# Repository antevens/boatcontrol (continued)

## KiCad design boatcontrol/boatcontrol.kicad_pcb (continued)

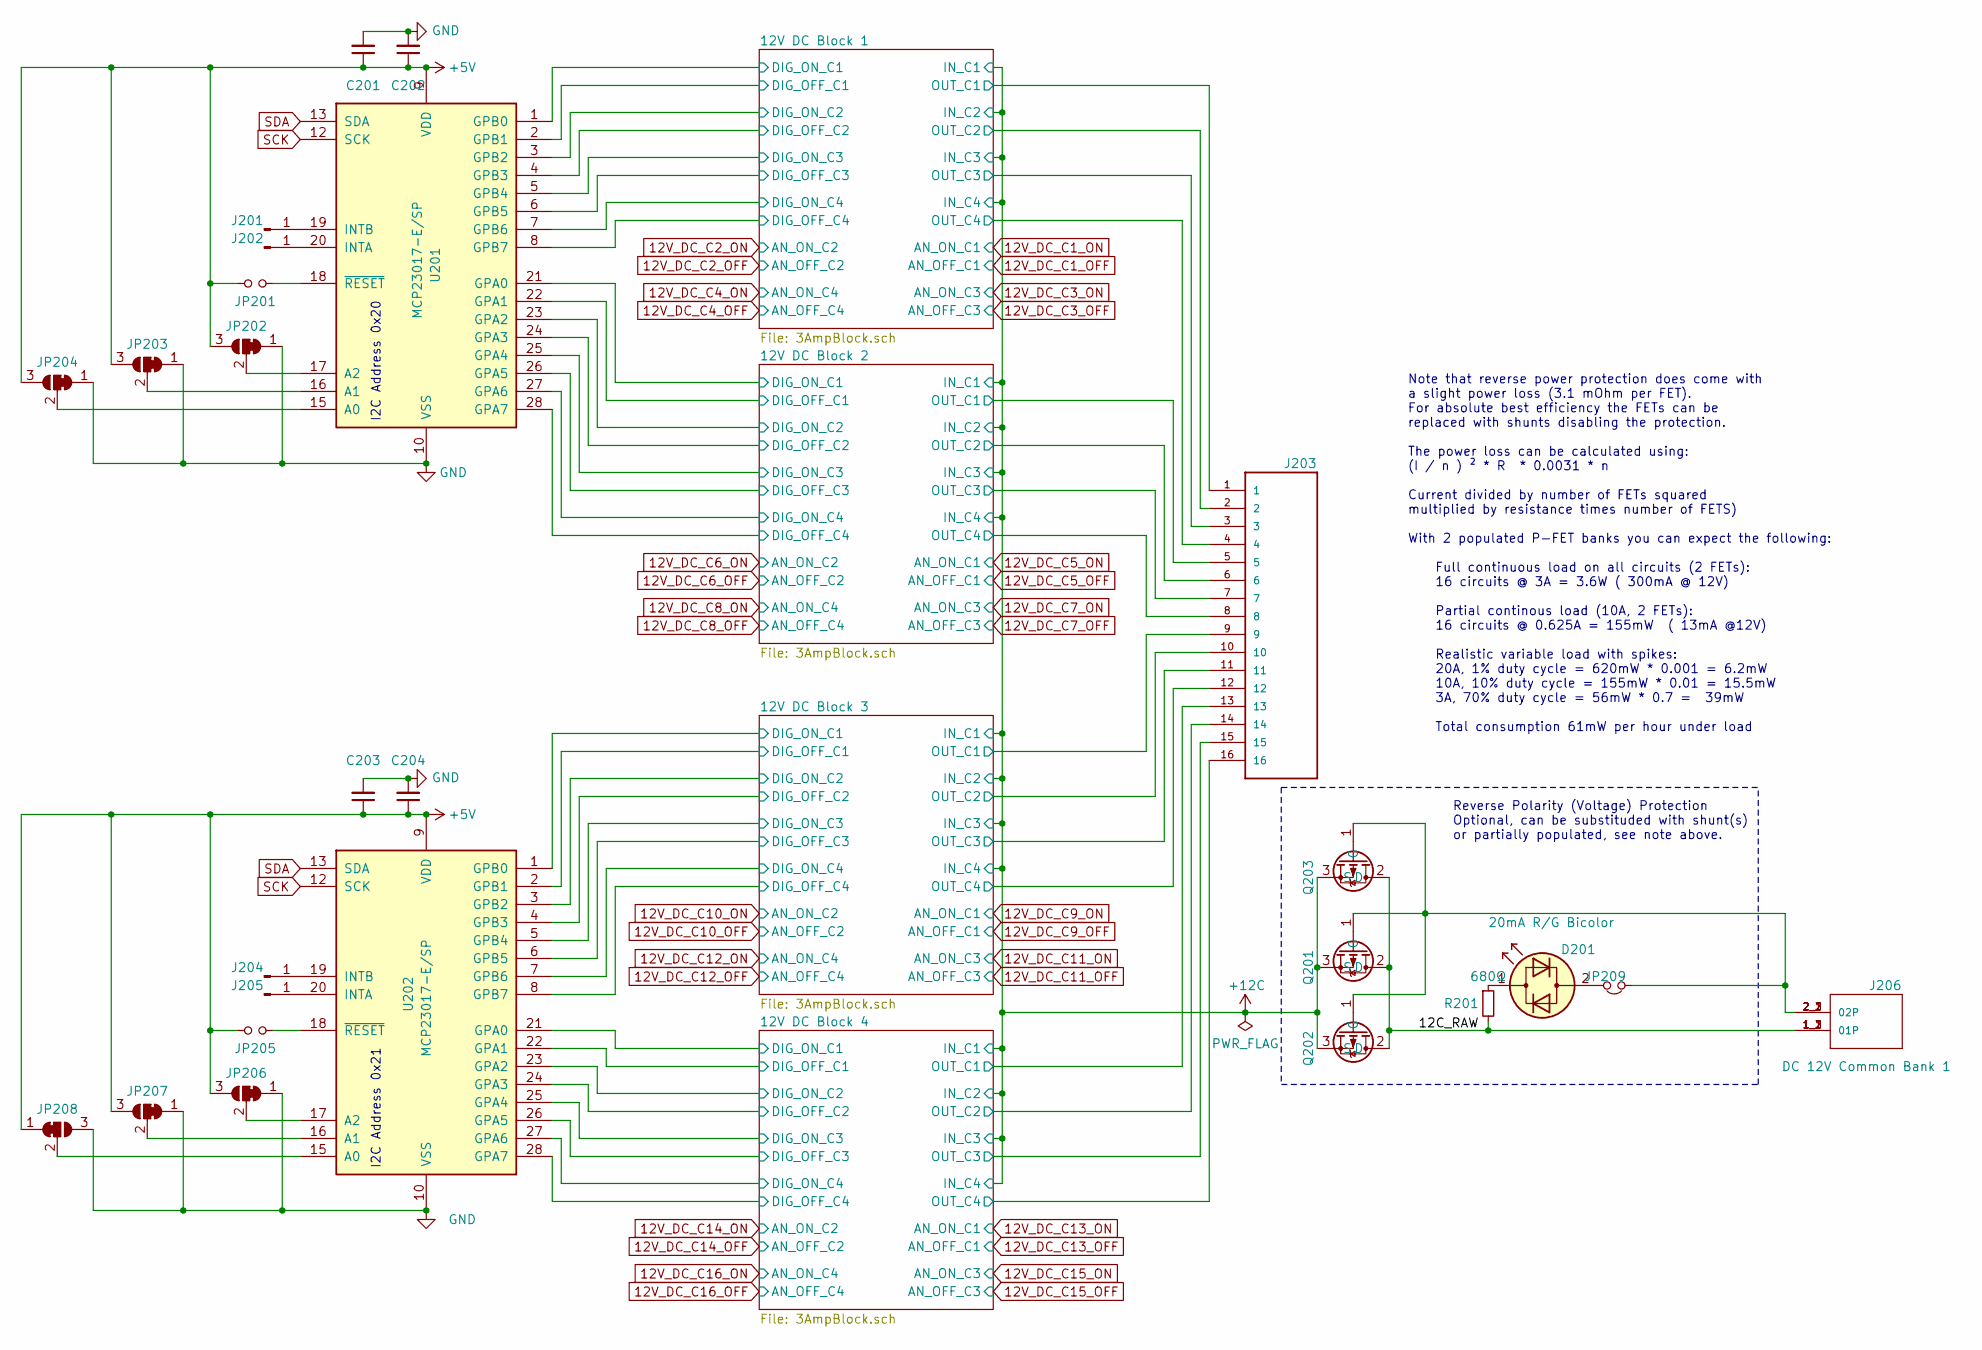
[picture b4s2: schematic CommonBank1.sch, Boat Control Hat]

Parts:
C201, C203: 10μF; C_Disc_D7.5mm_W5.0mm_P5.00mm
C202, C204: 0.1μF; C_Disc_D7.5mm_W5.0mm_P5.00mm
D201: 20mA R/G Bicolor; LED_D5.0mm
J201, J202, J204, J205: Conn_01x01_Male; PinHeader_1x01_P2.54mm_Vertical
J203: TBP01R2W-508-16BE; CUI_TBP01R2W-508-16BE
J206: TBL008V-1000-02BE; CUI_TBL008V-1000-02BE
JP201, JP205: Jumper_NO_Small; PinHeader_1x02_P2.54mm_Vertical
JP202, JP203, JP204, JP206, JP207, JP208: SolderJumper_3_Bridged12; SolderJumper-3_P1.3mm_Bridged12_RoundedPad1.0x1.5mm
JP209: Jumper_NC_Small; PinHeader_1x02_P2.54mm_Vertical
Q201, Q202, Q203: IPP120P04P4L-03; TO-220-3_Vertical
R201: 680Ω; R_Axial_DIN0207_L6.3mm_D2.5mm_P7.62mm_Horizontal
U201, U202: MCP23017-E/SP; DIP-28_W7.62mm

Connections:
+5V: C201.1, C202.1, C203.1, C204.1, JP201.2, JP202.3 (B), JP203.3 (B), JP204.3 (B), JP205.2, JP206.3 (B), JP207.3 (B), JP208.1 (A), U201.9 (VDD), U202.9 (VDD); also elsewhere on the board
+12C: Q201.3 (S), Q202.3 (S), Q203.3 (S); also elsewhere on the board
/12V DC Common Bank/12C_RAW: J206.1_1 (01P), J206.1_2 (01P), J206.1_3 (01P), Q201.2 (D), Q202.2 (D), Q203.2 (D), R201.2
/12V DC Common Bank/12V DC Block 1/DIG_OFF_C1: U201.2 (GPB1); also elsewhere on the board
/12V DC Common Bank/12V DC Block 1/DIG_OFF_C2: U201.4 (GPB3); also elsewhere on the board
/12V DC Common Bank/12V DC Block 1/DIG_OFF_C3: U201.6 (GPB5); also elsewhere on the board
/12V DC Common Bank/12V DC Block 1/DIG_OFF_C4: U201.8 (GPB7); also elsewhere on the board
/12V DC Common Bank/12V DC Block 1/DIG_ON_C1: U201.1 (GPB0); also elsewhere on the board
/12V DC Common Bank/12V DC Block 1/DIG_ON_C2: U201.3 (GPB2); also elsewhere on the board
/12V DC Common Bank/12V DC Block 1/DIG_ON_C3: U201.5 (GPB4); also elsewhere on the board
/12V DC Common Bank/12V DC Block 1/DIG_ON_C4: U201.7 (GPB6); also elsewhere on the board
/12V DC Common Bank/12V DC Block 1/OUT_C1: J203.1; also elsewhere on the board
/12V DC Common Bank/12V DC Block 1/OUT_C2: J203.2; also elsewhere on the board
/12V DC Common Bank/12V DC Block 1/OUT_C3: J203.3; also elsewhere on the board
/12V DC Common Bank/12V DC Block 1/OUT_C4: J203.4; also elsewhere on the board
/12V DC Common Bank/12V DC Block 2/DIG_OFF_C1: U201.22 (GPA1); also elsewhere on the board
/12V DC Common Bank/12V DC Block 2/DIG_OFF_C2: U201.24 (GPA3); also elsewhere on the board
/12V DC Common Bank/12V DC Block 2/DIG_OFF_C3: U201.26 (GPA5); also elsewhere on the board
/12V DC Common Bank/12V DC Block 2/DIG_OFF_C4: U201.28 (GPA7); also elsewhere on the board
/12V DC Common Bank/12V DC Block 2/DIG_ON_C1: U201.21 (GPA0); also elsewhere on the board
/12V DC Common Bank/12V DC Block 2/DIG_ON_C2: U201.23 (GPA2); also elsewhere on the board
/12V DC Common Bank/12V DC Block 2/DIG_ON_C3: U201.25 (GPA4); also elsewhere on the board
/12V DC Common Bank/12V DC Block 2/DIG_ON_C4: U201.27 (GPA6); also elsewhere on the board
/12V DC Common Bank/12V DC Block 2/OUT_C1: J203.5; also elsewhere on the board
/12V DC Common Bank/12V DC Block 2/OUT_C2: J203.6; also elsewhere on the board
/12V DC Common Bank/12V DC Block 2/OUT_C3: J203.7; also elsewhere on the board
/12V DC Common Bank/12V DC Block 2/OUT_C4: J203.8; also elsewhere on the board
/12V DC Common Bank/12V DC Block 3/DIG_OFF_C1: U202.2 (GPB1); also elsewhere on the board
/12V DC Common Bank/12V DC Block 3/DIG_OFF_C2: U202.4 (GPB3); also elsewhere on the board
/12V DC Common Bank/12V DC Block 3/DIG_OFF_C3: U202.6 (GPB5); also elsewhere on the board
/12V DC Common Bank/12V DC Block 3/DIG_OFF_C4: U202.8 (GPB7); also elsewhere on the board
/12V DC Common Bank/12V DC Block 3/DIG_ON_C1: U202.1 (GPB0); also elsewhere on the board
/12V DC Common Bank/12V DC Block 3/DIG_ON_C2: U202.3 (GPB2); also elsewhere on the board
/12V DC Common Bank/12V DC Block 3/DIG_ON_C3: U202.5 (GPB4); also elsewhere on the board
/12V DC Common Bank/12V DC Block 3/DIG_ON_C4: U202.7 (GPB6); also elsewhere on the board
/12V DC Common Bank/12V DC Block 3/OUT_C1: J203.9; also elsewhere on the board
/12V DC Common Bank/12V DC Block 3/OUT_C2: J203.10; also elsewhere on the board
/12V DC Common Bank/12V DC Block 3/OUT_C3: J203.11; also elsewhere on the board
/12V DC Common Bank/12V DC Block 3/OUT_C4: J203.12; also elsewhere on the board
/12V DC Common Bank/12V DC Block 4/DIG_OFF_C1: U202.22 (GPA1); also elsewhere on the board
/12V DC Common Bank/12V DC Block 4/DIG_OFF_C2: U202.24 (GPA3); also elsewhere on the board
/12V DC Common Bank/12V DC Block 4/DIG_OFF_C3: U202.26 (GPA5); also elsewhere on the board
/12V DC Common Bank/12V DC Block 4/DIG_OFF_C4: U202.28 (GPA7); also elsewhere on the board
/12V DC Common Bank/12V DC Block 4/DIG_ON_C1: U202.21 (GPA0); also elsewhere on the board
/12V DC Common Bank/12V DC Block 4/DIG_ON_C2: U202.23 (GPA2); also elsewhere on the board
/12V DC Common Bank/12V DC Block 4/DIG_ON_C3: U202.25 (GPA4); also elsewhere on the board
/12V DC Common Bank/12V DC Block 4/DIG_ON_C4: U202.27 (GPA6); also elsewhere on the board
/12V DC Common Bank/12V DC Block 4/OUT_C1: J203.13; also elsewhere on the board
/12V DC Common Bank/12V DC Block 4/OUT_C2: J203.14; also elsewhere on the board
/12V DC Common Bank/12V DC Block 4/OUT_C3: J203.15; also elsewhere on the board
/12V DC Common Bank/12V DC Block 4/OUT_C4: J203.16; also elsewhere on the board
GND: C201.2, C202.2, C203.2, C204.2, JP202.1 (A), JP203.1 (A), JP204.1 (A), JP206.1 (A), JP207.1 (A), JP208.3 (B), U201.10 (VSS), U202.10 (VSS); also elsewhere on the board
unnamed: D201.1 (KA), R201.1
unnamed: D201.2 (AK), JP209.2
unnamed: J201.1, U201.19 (INTB)
unnamed: J202.1, U201.20 (INTA)
unnamed: J204.1, U202.19 (INTB)
unnamed: J205.1, U202.20 (INTA)
unnamed: J206.2_1 (02P), J206.2_2 (02P), J206.2_3 (02P), JP209.1, Q201.1 (G), Q202.1 (G), Q203.1 (G)
unnamed: JP201.1, U201.18 (~RESET~)
unnamed: JP202.2 (C), U201.17 (A2)
unnamed: JP203.2 (C), U201.16 (A1)
unnamed: JP204.2 (C), U201.15 (A0)
unnamed: JP205.1, U202.18 (~RESET~)
unnamed: JP206.2 (C), U202.17 (A2)
unnamed: JP207.2 (C), U202.16 (A1)
unnamed: JP208.2 (C), U202.15 (A0)
SCK: U201.12 (SCK), U202.12 (SCK); also elsewhere on the board
SDA: U201.13 (SDA), U202.13 (SDA); also elsewhere on the board

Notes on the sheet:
I2C Address 0x20
I2C Address 0x21
Reverse Polarity (Voltage) Protection Optional, can be substituded with shunt(s) or partially populated, see note above.
Note that reverse power protection does come with a slight power loss (3.1 mOhm per FET). For absolute best efficiency the FETs can be replaced with shunts disabling the protection. The power loss can be calculated using: (I / n ) ² * R * 0.0031 * n Current divided by number of FETs squared multipl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

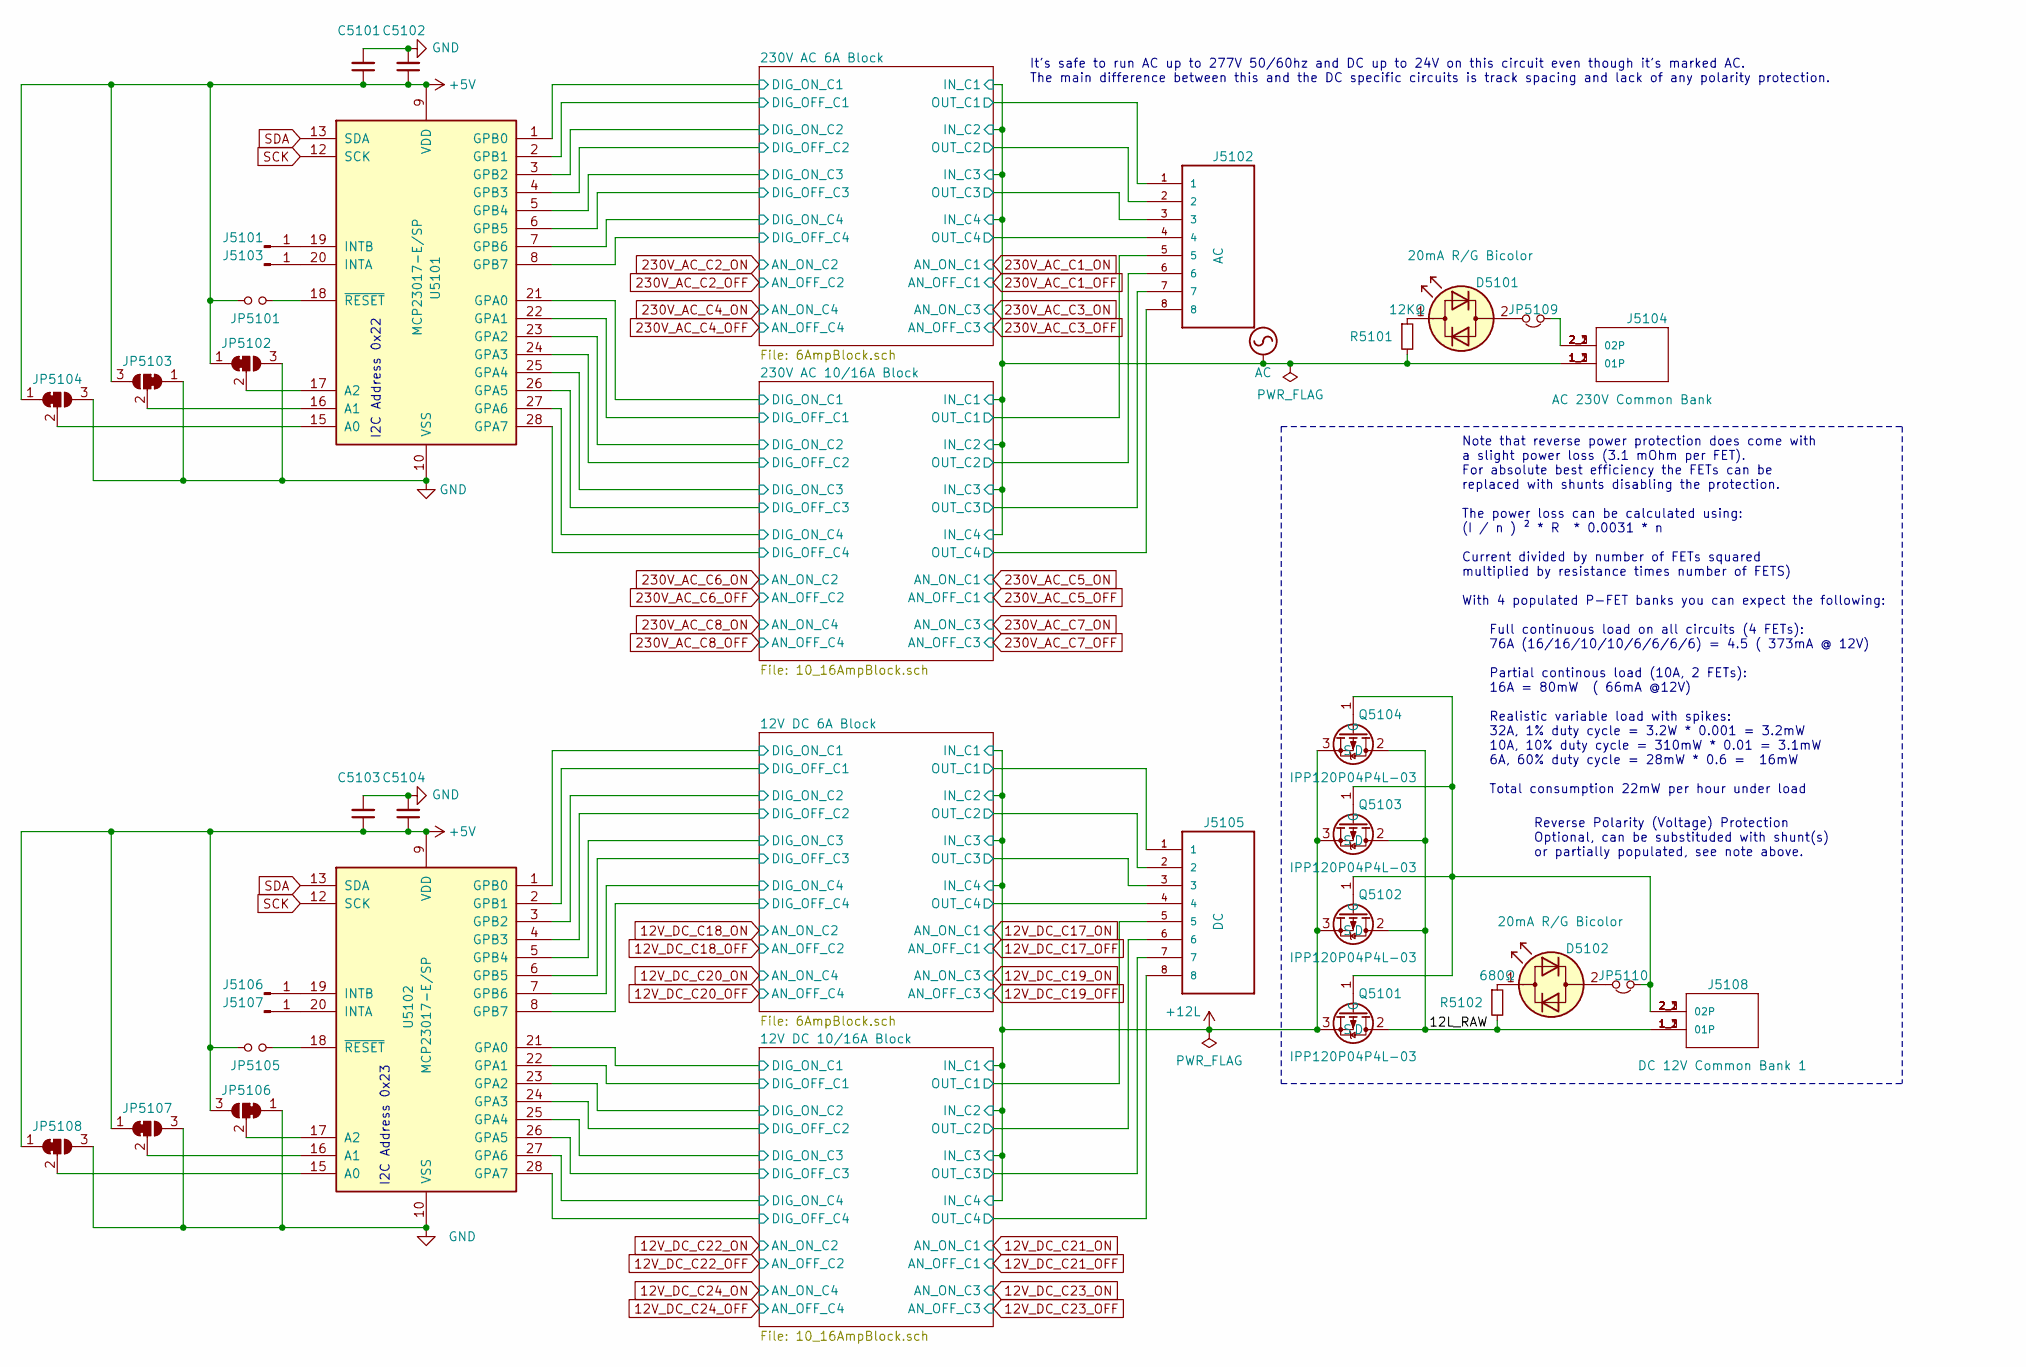
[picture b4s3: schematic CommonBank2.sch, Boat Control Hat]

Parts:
C5101, C5103: 10μF; C_Disc_D7.5mm_W5.0mm_P5.00mm
C5102, C5104: 0.1μF; C_Disc_D7.5mm_W5.0mm_P5.00mm
D5101, D5102: 20mA R/G Bicolor; LED_D5.0mm
J5101, J5103, J5106, J5107: Conn_01x01_Male; PinHeader_1x01_P2.54mm_Vertical
J5102, J5105: TBP01R2W-508-08BE; CUI_TBP01R2W-508-08BE
J5104, J5108: TBL008V-1000-02BE; CUI_TBL008V-1000-02BE
JP5101, JP5105: Jumper_NO_Small; PinHeader_1x02_P2.54mm_Vertical
JP5102, JP5103, JP5104, JP5106, JP5107, JP5108: SolderJumper_3_Bridged12; SolderJumper-3_P1.3mm_Bridged12_RoundedPad1.0x1.5mm
JP5109, JP5110: Jumper_NC_Small; PinHeader_1x02_P2.54mm_Vertical
Q5101, Q5102, Q5103, Q5104: IPP120P04P4L-03; TO-220-3_Vertical
R5101: 12KΩ; R_Axial_DIN0207_L6.3mm_D2.5mm_P7.62mm_Horizontal
R5102: 680Ω; R_Axial_DIN0207_L6.3mm_D2.5mm_P7.62mm_Horizontal
U5101, U5102: MCP23017-E/SP; DIP-28_W7.62mm

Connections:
+5V: C5101.1, C5102.1, C5103.1, C5104.1, JP5101.2, JP5102.1 (A), JP5103.3 (B), JP5104.1 (A), JP5105.2, JP5106.3 (B), JP5107.1 (A), JP5108.1 (A), U5101.9 (VDD), U5102.9 (VDD); also elsewhere on the board
+12L: Q5101.3 (S), Q5102.3 (S), Q5103.3 (S), Q5104.3 (S); also elsewhere on the board
/Mixed 12V DC / 230V AC Common Bank/12L_RAW: J5108.1_1 (01P), J5108.1_2 (01P), J5108.1_3 (01P), Q5101.2 (D), Q5102.2 (D), Q5103.2 (D), Q5104.2 (D), R5102.2
/Mixed 12V DC / 230V AC Common Bank/12V DC 6A Block/DIG_OFF_C1: U5102.2 (GPB1); also elsewhere on the board
/Mixed 12V DC / 230V AC Common Bank/12V DC 6A Block/DIG_OFF_C2: U5102.4 (GPB3); also elsewhere on the board
/Mixed 12V DC / 230V AC Common Bank/12V DC 6A Block/DIG_OFF_C3: U5102.6 (GPB5); also elsewhere on the board
/Mixed 12V DC / 230V AC Common Bank/12V DC 6A Block/DIG_OFF_C4: U5102.8 (GPB7); also elsewhere on the board
/Mixed 12V DC / 230V AC Common Bank/12V DC 6A Block/DIG_ON_C1: U5102.1 (GPB0); also elsewhere on the board
/Mixed 12V DC / 230V AC Common Bank/12V DC 6A Block/DIG_ON_C2: U5102.3 (GPB2); also elsewhere on the board
/Mixed 12V DC / 230V AC Common Bank/12V DC 6A Block/DIG_ON_C3: U5102.5 (GPB4); also elsewhere on the board
/Mixed 12V DC / 230V AC Common Bank/12V DC 6A Block/DIG_ON_C4: U5102.7 (GPB6); also elsewhere on the board
/Mixed 12V DC / 230V AC Common Bank/12V DC 6A Block/OUT_C1: J5105.1; also elsewhere on the board
/Mixed 12V DC / 230V AC Common Bank/12V DC 6A Block/OUT_C2: J5105.2; also elsewhere on the board
/Mixed 12V DC / 230V AC Common Bank/12V DC 6A Block/OUT_C3: J5105.3; also elsewhere on the board
/Mixed 12V DC / 230V AC Common Bank/12V DC 6A Block/OUT_C4: J5105.4; also elsewhere on the board
/Mixed 12V DC / 230V AC Common Bank/12V DC 10/16A Block/DIG_OFF_C1: U5102.22 (GPA1); also elsewhere on the board
/Mixed 12V DC / 230V AC Common Bank/12V DC 10/16A Block/DIG_OFF_C2: U5102.24 (GPA3); also elsewhere on the board
/Mixed 12V DC / 230V AC Common Bank/12V DC 10/16A Block/DIG_OFF_C3: U5102.26 (GPA5); also elsewhere on the board
/Mixed 12V DC / 230V AC Common Bank/12V DC 10/16A Block/DIG_OFF_C4: U5102.28 (GPA7); also elsewhere on the board
/Mixed 12V DC / 230V AC Common Bank/12V DC 10/16A Block/DIG_ON_C1: U5102.21 (GPA0); also elsewhere on the board
/Mixed 12V DC / 230V AC Common Bank/12V DC 10/16A Block/DIG_ON_C2: U5102.23 (GPA2); also elsewhere on the board
/Mixed 12V DC / 230V AC Common Bank/12V DC 10/16A Block/DIG_ON_C3: U5102.25 (GPA4); also elsewhere on the board
/Mixed 12V DC / 230V AC Common Bank/12V DC 10/16A Block/DIG_ON_C4: U5102.27 (GPA6); also elsewhere on the board
/Mixed 12V DC / 230V AC Common Bank/12V DC 10/16A Block/OUT_C1: J5105.5; also elsewhere on the board
/Mixed 12V DC / 230V AC Common Bank/12V DC 10/16A Block/OUT_C2: J5105.6; also elsewhere on the board
/Mixed 12V DC / 230V AC Common Bank/12V DC 10/16A Block/OUT_C3: J5105.7; also elsewhere on the board
/Mixed 12V DC / 230V AC Common Bank/12V DC 10/16A Block/OUT_C4: J5105.8; also elsewhere on the board
/Mixed 12V DC / 230V AC Common Bank/230V AC 6A Block/DIG_OFF_C1: U5101.2 (GPB1); also elsewhere on the board
/Mixed 12V DC / 230V AC Common Bank/230V AC 6A Block/DIG_OFF_C2: U5101.4 (GPB3); also elsewhere on the board
/Mixed 12V DC / 230V AC Common Bank/230V AC 6A Block/DIG_OFF_C3: U5101.6 (GPB5); also elsewhere on the board
/Mixed 12V DC / 230V AC Common Bank/230V AC 6A Block/DIG_OFF_C4: U5101.8 (GPB7); also elsewhere on the board
/Mixed 12V DC / 230V AC Common Bank/230V AC 6A Block/DIG_ON_C1: U5101.1 (GPB0); also elsewhere on the board
/Mixed 12V DC / 230V AC Common Bank/230V AC 6A Block/DIG_ON_C2: U5101.3 (GPB2); also elsewhere on the board
/Mixed 12V DC / 230V AC Common Bank/230V AC 6A Block/DIG_ON_C3: U5101.5 (GPB4); also elsewhere on the board
/Mixed 12V DC / 230V AC Common Bank/230V AC 6A Block/DIG_ON_C4: U5101.7 (GPB6); also elsewhere on the board
/Mixed 12V DC / 230V AC Common Bank/230V AC 6A Block/OUT_C1: J5102.1; also elsewhere on the board
/Mixed 12V DC / 230V AC Common Bank/230V AC 6A Block/OUT_C2: J5102.2; also elsewhere on the board
/Mixed 12V DC / 230V AC Common Bank/230V AC 6A Block/OUT_C3: J5102.3; also elsewhere on the board
/Mixed 12V DC / 230V AC Common Bank/230V AC 6A Block/OUT_C4: J5102.4; also elsewhere on the board
/Mixed 12V DC / 230V AC Common Bank/230V AC 10/16A Block/DIG_OFF_C1: U5101.22 (GPA1); also elsewhere on the board
/Mixed 12V DC / 230V AC Common Bank/230V AC 10/16A Block/DIG_OFF_C2: U5101.24 (GPA3); also elsewhere on the board
/Mixed 12V DC / 230V AC Common Bank/230V AC 10/16A Block/DIG_OFF_C3: U5101.26 (GPA5); also elsewhere on the board
/Mixed 12V DC / 230V AC Common Bank/230V AC 10/16A Block/DIG_OFF_C4: U5101.28 (GPA7); also elsewhere on the board
/Mixed 12V DC / 230V AC Common Bank/230V AC 10/16A Block/DIG_ON_C1: U5101.21 (GPA0); also elsewhere on the board
/Mixed 12V DC / 230V AC Common Bank/230V AC 10/16A Block/DIG_ON_C2: U5101.23 (GPA2); also elsewhere on the board
/Mixed 12V DC / 230V AC Common Bank/230V AC 10/16A Block/DIG_ON_C3: U5101.25 (GPA4); also elsewhere on the board
/Mixed 12V DC / 230V AC Common Bank/230V AC 10/16A Block/DIG_ON_C4: U5101.27 (GPA6); also elsewhere on the board
/Mixed 12V DC / 230V AC Common Bank/230V AC 10/16A Block/OUT_C1: J5102.5; also elsewhere on the board
/Mixed 12V DC / 230V AC Common Bank/230V AC 10/16A Block/OUT_C2: J5102.6; also elsewhere on the board
/Mixed 12V DC / 230V AC Common Bank/230V AC 10/16A Block/OUT_C3: J5102.7; also elsewhere on the board
/Mixed 12V DC / 230V AC Common Bank/230V AC 10/16A Block/OUT_C4: J5102.8; also elsewhere on the board
AC: J5104.1_1 (01P), J5104.1_2 (01P), J5104.1_3 (01P), R5101.2; also elsewhere on the board
GND: C5101.2, C5102.2, C5103.2, C5104.2, JP5102.3 (B), JP5103.1 (A), JP5104.3 (B), JP5106.1 (A), JP5107.3 (B), JP5108.3 (B), U5101.10 (VSS), U5102.10 (VSS); also elsewhere on the board
unnamed: D5101.1 (KA), R5101.1
unnamed: D5101.2 (AK), JP5109.2
unnamed: D5102.1 (KA), R5102.1
unnamed: D5102.2 (AK), JP5110.2
unnamed: J5101.1, U5101.19 (INTB)
unnamed: J5103.1, U5101.20 (INTA)
unnamed: J5104.2_1 (02P), J5104.2_2 (02P), J5104.2_3 (02P), JP5109.1
unnamed: J5106.1, U5102.19 (INTB)
unnamed: J5107.1, U5102.20 (INTA)
unnamed: J5108.2_1 (02P), J5108.2_2 (02P), J5108.2_3 (02P), JP5110.1, Q5101.1 (G), Q5102.1 (G), Q5103.1 (G), Q5104.1 (G)
unnamed: JP5101.1, U5101.18 (~RESET~)
unnamed: JP5102.2 (C), U5101.17 (A2)
unnamed: JP5103.2 (C), U5101.16 (A1)
unnamed: JP5104.2 (C), U5101.15 (A0)
unnamed: JP5105.1, U5102.18 (~RESET~)
unnamed: JP5106.2 (C), U5102.17 (A2)
unnamed: JP5107.2 (C), U5102.16 (A1)
unnamed: JP5108.2 (C), U5102.15 (A0)
SCK: U5101.12 (SCK), U5102.12 (SCK); also elsewhere on the board
SDA: U5101.13 (SDA), U5102.13 (SDA); also elsewhere on the board

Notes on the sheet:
I2C Address 0x23
I2C Address 0x22
It's safe to run AC up to 277V 50/60hz and DC up to 24V on this circuit even though it's marked AC. The main difference between this and the DC specific circuits is track spacing and lack of any polarity protection.
Reverse Polarity (Voltage) Protection Optional, can be substituded with shunt(s) or partially populated, see note above.
Note that reverse power protection does come with a slight power loss (3.1 mOhm per FET). For absolute best efficiency the FETs can be replaced with shunts disabling the protection. The power loss can be calculated using: (I / n ) ² * R * 0.0031 * n Current divided by number of FETs squared multipl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

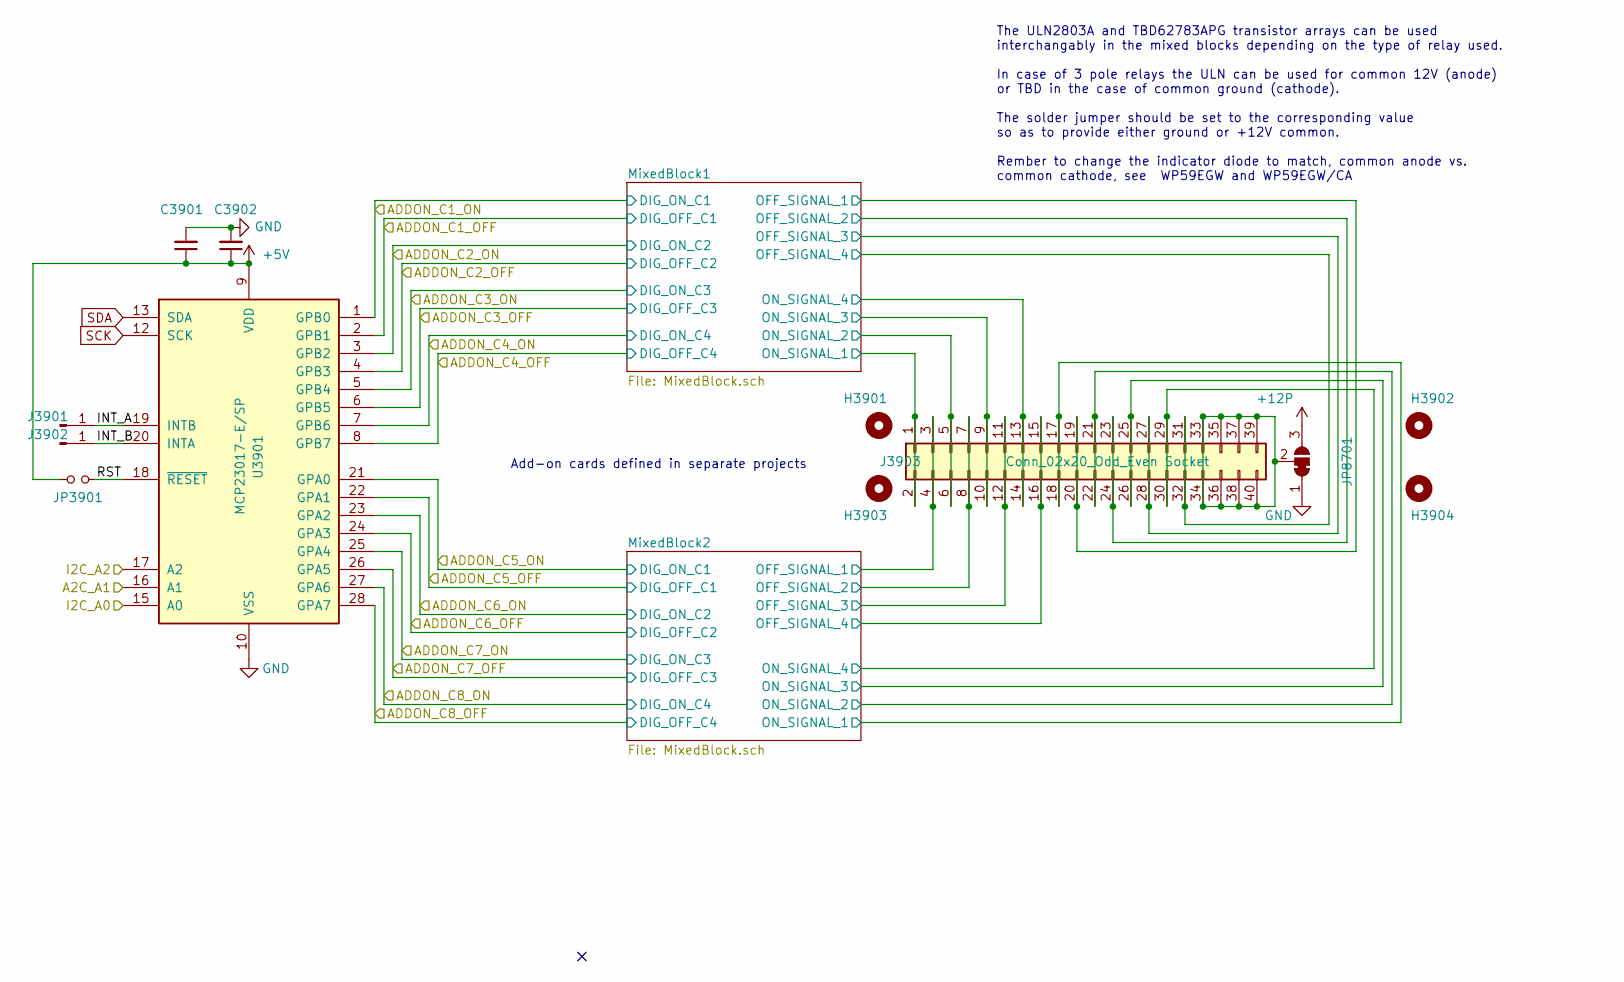
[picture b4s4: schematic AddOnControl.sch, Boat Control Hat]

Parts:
C8801: 10uF; C_Disc_D7.5mm_W5.0mm_P5.00mm
C8802: 0.1uF; C_Disc_D7.5mm_W5.0mm_P5.00mm
H3901, H3902, H3903, H3904: MountingHole; MountingHole_3mm
J3901, J3902: Conn_01x01_Male; PinHeader_1x01_P2.54mm_Vertical
J3903: Conn_02x20_Odd_Even Socket; PinHeader_2x20_P2.54mm_Vertical
JP210: SolderJumper_3_Bridged12; SolderJumper-3_P1.3mm_Open_RoundedPad3.0x4.5mm_NumberLabels
JP3901: Jumper_NO_Small; PinHeader_1x02_P2.54mm_Vertical
U3901: MCP23017-E/SP; DIP-28_W7.62mm

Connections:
+5V: C8801.1, C8802.1, JP3901.2, U3901.9 (VDD); also elsewhere on the board
+12P: JP210.3 (B); also elsewhere on the board
/Add-On Relay Board 1/A2C_A1: U3901.16 (A1); also elsewhere on the board
/Add-On Relay Board 1/ADDON_C1_OFF: U3901.2 (GPB1); also elsewhere on the board
/Add-On Relay Board 1/ADDON_C1_ON: U3901.1 (GPB0); also elsewhere on the board
/Add-On Relay Board 1/ADDON_C2_OFF: U3901.4 (GPB3); also elsewhere on the board
/Add-On Relay Board 1/ADDON_C2_ON: U3901.3 (GPB2); also elsewhere on the board
/Add-On Relay Board 1/ADDON_C3_OFF: U3901.6 (GPB5); also elsewhere on the board
/Add-On Relay Board 1/ADDON_C3_ON: U3901.5 (GPB4); also elsewhere on the board
/Add-On Relay Board 1/ADDON_C4_OFF: U3901.8 (GPB7); also elsewhere on the board
/Add-On Relay Board 1/ADDON_C4_ON: U3901.7 (GPB6); also elsewhere on the board
/Add-On Relay Board 1/ADDON_C5_OFF: U3901.22 (GPA1); also elsewhere on the board
/Add-On Relay Board 1/ADDON_C5_ON: U3901.21 (GPA0); also elsewhere on the board
/Add-On Relay Board 1/ADDON_C6_OFF: U3901.24 (GPA3); also elsewhere on the board
/Add-On Relay Board 1/ADDON_C6_ON: U3901.23 (GPA2); also elsewhere on the board
/Add-On Relay Board 1/ADDON_C7_OFF: U3901.26 (GPA5); also elsewhere on the board
/Add-On Relay Board 1/ADDON_C7_ON: U3901.25 (GPA4); also elsewhere on the board
/Add-On Relay Board 1/ADDON_C8_OFF: U3901.28 (GPA7); also elsewhere on the board
/Add-On Relay Board 1/ADDON_C8_ON: U3901.27 (GPA6); also elsewhere on the board
/Add-On Relay Board 1/I2C_A0: U3901.15 (A0); also elsewhere on the board
/Add-On Relay Board 1/I2C_A2: U3901.17 (A2); also elsewhere on the board
/Add-On Relay Board 1/INT_A: J3901.1, U3901.19 (INTB)
/Add-On Relay Board 1/INT_B: J3902.1, U3901.20 (INTA)
/Add-On Relay Board 1/MixedBlock1/OFF_SIGNAL_1: J3903.19, J3903.20; also elsewhere on the board
/Add-On Relay Board 1/MixedBlock1/OFF_SIGNAL_2: J3903.23, J3903.24; also elsewhere on the board
/Add-On Relay Board 1/MixedBlock1/OFF_SIGNAL_3: J3903.27, J3903.28; also elsewhere on the board
/Add-On Relay Board 1/MixedBlock1/OFF_SIGNAL_4: J3903.31, J3903.32; also elsewhere on the board
/Add-On Relay Board 1/MixedBlock1/ON_SIGNAL_1: J3903.1, J3903.2; also elsewhere on the board
/Add-On Relay Board 1/MixedBlock1/ON_SIGNAL_2: J3903.5, J3903.6; also elsewhere on the board
/Add-On Relay Board 1/MixedBlock1/ON_SIGNAL_3: J3903.9, J3903.10; also elsewhere on the board
/Add-On Relay Board 1/MixedBlock1/ON_SIGNAL_4: J3903.13, J3903.14; also elsewhere on the board
/Add-On Relay Board 1/MixedBlock2/OFF_SIGNAL_1: J3903.3, J3903.4; also elsewhere on the board
/Add-On Relay Board 1/MixedBlock2/OFF_SIGNAL_2: J3903.7, J3903.8; also elsewhere on the board
/Add-On Relay Board 1/MixedBlock2/OFF_SIGNAL_3: J3903.11, J3903.12; also elsewhere on the board
/Add-On Relay Board 1/MixedBlock2/OFF_SIGNAL_4: J3903.15, J3903.16; also elsewhere on the board
/Add-On Relay Board 1/MixedBlock2/ON_SIGNAL_1: J3903.17, J3903.18; also elsewhere on the board
/Add-On Relay Board 1/MixedBlock2/ON_SIGNAL_2: J3903.21, J3903.22; also elsewhere on the board
/Add-On Relay Board 1/MixedBlock2/ON_SIGNAL_3: J3903.25, J3903.26; also elsewhere on the board
/Add-On Relay Board 1/MixedBlock2/ON_SIGNAL_4: J3903.29, J3903.30; also elsewhere on the board
/Add-On Relay Board 1/RST: JP3901.1, U3901.18 (~RESET~)
GND: C8801.2, C8802.2, JP210.1 (A), U3901.10 (VSS); also elsewhere on the board
SCK: U3901.12 (SCK); also elsewhere on the board
SDA: U3901.13 (SDA); also elsewhere on the board

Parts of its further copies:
C3901: 10uF; C_Disc_D7.5mm_W5.0mm_P5.00mm
C3902: 0.1uF; C_Disc_D7.5mm_W5.0mm_P5.00mm
H8801, H8802, H8803, H8804: MountingHole; MountingHole_3mm
J8801, J8802: Conn_01x01_Male; PinHeader_1x01_P2.54mm_Vertical
J8803: Conn_02x20_Odd_Even Socket; PinHeader_2x20_P2.54mm_Vertical
JP8701: SolderJumper_3_Bridged12; SolderJumper-3_P1.3mm_Open_RoundedPad3.0x4.5mm_NumberLabels
JP8804: Jumper_NO_Small; PinHeader_1x02_P2.54mm_Vertical
U8801: MCP23017-E/SP; DIP-28_W7.62mm

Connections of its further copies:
+5V: C3901.1, C3902.1, JP8804.2, U8801.9 (VDD); also elsewhere on the board
+12P: JP8701.3 (B); also elsewhere on the board
/Add-On Relay Board 2/A2C_A1: U8801.16 (A1); also elsewhere on the board
/Add-On Relay Board 2/ADDON_C1_OFF: U8801.2 (GPB1); also elsewhere on the board
/Add-On Relay Board 2/ADDON_C1_ON: U8801.1 (GPB0); also elsewhere on the board
/Add-On Relay Board 2/ADDON_C2_OFF: U8801.4 (GPB3); also elsewhere on the board
/Add-On Relay Board 2/ADDON_C2_ON: U8801.3 (GPB2); also elsewhere on the board
/Add-On Relay Board 2/ADDON_C3_OFF: U8801.6 (GPB5); also elsewhere on the board
/Add-On Relay Board 2/ADDON_C3_ON: U8801.5 (GPB4); also elsewhere on the board
/Add-On Relay Board 2/ADDON_C4_OFF: U8801.8 (GPB7); also elsewhere on the board
/Add-On Relay Board 2/ADDON_C4_ON: U8801.7 (GPB6); also elsewhere on the board
/Add-On Relay Board 2/ADDON_C5_OFF: U8801.22 (GPA1); also elsewhere on the board
/Add-On Relay Board 2/ADDON_C5_ON: U8801.21 (GPA0); also elsewhere on the board
/Add-On Relay Board 2/ADDON_C6_OFF: U8801.24 (GPA3); also elsewhere on the board
/Add-On Relay Board 2/ADDON_C6_ON: U8801.23 (GPA2); also elsewhere on the board
/Add-On Relay Board 2/ADDON_C7_OFF: U8801.26 (GPA5); also elsewhere on the board
/Add-On Relay Board 2/ADDON_C7_ON: U8801.25 (GPA4); also elsewhere on the board
/Add-On Relay Board 2/ADDON_C8_OFF: U8801.28 (GPA7); also elsewhere on the board
/Add-On Relay Board 2/ADDON_C8_ON: U8801.27 (GPA6); also elsewhere on the board
/Add-On Relay Board 2/I2C_A0: U8801.15 (A0); also elsewhere on the board
/Add-On Relay Board 2/I2C_A2: U8801.17 (A2); also elsewhere on the board
/Add-On Relay Board 2/INT_A: J8801.1, U8801.19 (INTB)
/Add-On Relay Board 2/INT_B: J8802.1, U8801.20 (INTA)
/Add-On Relay Board 2/MixedBlock1/OFF_SIGNAL_1: J8803.19, J8803.20; also elsewhere on the board
/Add-On Relay Board 2/MixedBlock1/OFF_SIGNAL_2: J8803.23, J8803.24; also elsewhere on the board
/Add-On Relay Board 2/MixedBlock1/OFF_SIGNAL_3: J8803.27, J8803.28; also elsewhere on the board
/Add-On Relay Board 2/MixedBlock1/OFF_SIGNAL_4: J8803.31, J8803.32; also elsewhere on the board
/Add-On Relay Board 2/MixedBlock1/ON_SIGNAL_1: J8803.1, J8803.2; also elsewhere on the board
/Add-On Relay Board 2/MixedBlock1/ON_SIGNAL_2: J8803.5, J8803.6; also elsewhere on the board
/Add-On Relay Board 2/MixedBlock1/ON_SIGNAL_3: J8803.9, J8803.10; also elsewhere on the board
/Add-On Relay Board 2/MixedBlock1/ON_SIGNAL_4: J8803.13, J8803.14; also elsewhere on the board
/Add-On Relay Board 2/MixedBlock2/OFF_SIGNAL_1: J8803.3, J8803.4; also elsewhere on the board
/Add-On Relay Board 2/MixedBlock2/OFF_SIGNAL_2: J8803.7, J8803.8; also elsewhere on the board
/Add-On Relay Board 2/MixedBlock2/OFF_SIGNAL_3: J8803.11, J8803.12; also elsewhere on the board
/Add-On Relay Board 2/MixedBlock2/OFF_SIGNAL_4: J8803.15, J8803.16; also elsewhere on the board
/Add-On Relay Board 2/MixedBlock2/ON_SIGNAL_1: J8803.17, J8803.18; also elsewhere on the board
/Add-On Relay Board 2/MixedBlock2/ON_SIGNAL_2: J8803.21, J8803.22; also elsewhere on the board
/Add-On Relay Board 2/MixedBlock2/ON_SIGNAL_3: J8803.25, J8803.26; also elsewhere on the board
/Add-On Relay Board 2/MixedBlock2/ON_SIGNAL_4: J8803.29, J8803.30; also elsewhere on the board
/Add-On Relay Board 2/RST: JP8804.1, U8801.18 (~RESET~)
GND: C3901.2, C3902.2, JP8701.1 (A), U8801.10 (VSS); also elsewhere on the board
SCK: U8801.12 (SCK); also elsewhere on the board
SDA: U8801.13 (SDA); also elsewhere on the board

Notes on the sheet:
Add-on cards defined in separate projects
The ULN2803A and TBD62783APG transistor arrays can be used interchangably in the mixed blocks depending on the type of relay used. In case of 3 pole relays the ULN can be used for common 12V (anode) or TBD in the case of common ground (cathode). The solder jumper should be set to the corresponding 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
